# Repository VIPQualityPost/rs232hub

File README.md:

# rs232hub
This is a small project to make a USB-RS232 four port hub for use with SCPI commands for making an easy, automated testing controller. 
I successfully made the prototype with just one channel, but for the final design I want to incorporate a 4 port USB hub controller so I can have several devices connected at once.
I don't need USB3.0 speed so this will not include that, but it will feature a USB-C port to be consistent with other designs I have made (and I still have several connectors left over from previous projects)

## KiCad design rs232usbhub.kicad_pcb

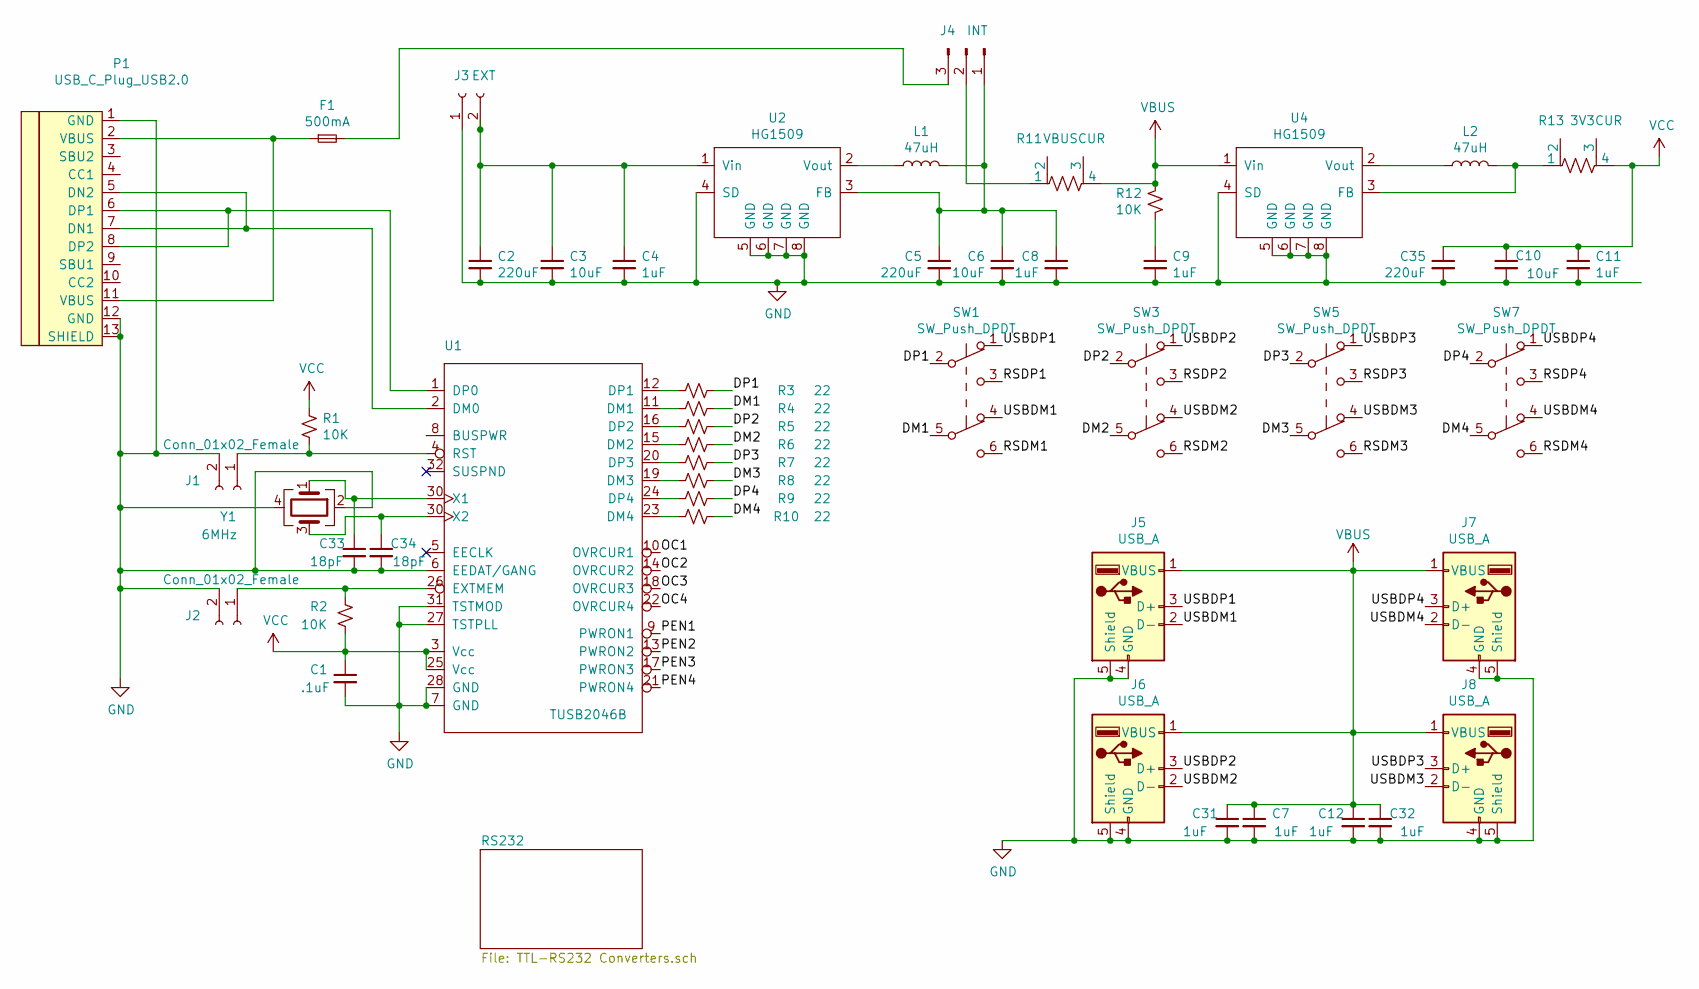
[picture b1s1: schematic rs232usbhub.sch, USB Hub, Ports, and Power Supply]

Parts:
C1: .1uF; C_0402_1005Metric_Pad0.74x0.62mm_HandSolder
C2, C5, C35: 220uF; CP_Elec_8x10.5
C3, C6, C10: 10uF; CP_Elec_4x5.4
C4, C7, C8, C9, C11, C12, C31, C32: 1uF; C_0402_1005Metric_Pad0.74x0.62mm_HandSolder
C33, C34: 18pF; C_0402_1005Metric_Pad0.74x0.62mm_HandSolder
F1: 500mA; C_0402_1005Metric_Pad0.74x0.62mm_HandSolder
J1, J2: Conn_01x02_Female; PinHeader_1x02_P1.00mm_Vertical
J3: EXT; BarrelJack_CLIFF_FC681465S_SMT_Horizontal
J4: INT; PinHeader_1x03_P2.54mm_Vertical
J5, J6, J7, J8: USB_A; USBA2LCSC109355
L1, L2: 47uH; L_12x12mm_H4.5mm
P1: USB_C_Plug_USB2.0; HRO-TYPE-C-31-M-12-HandSoldering
R1, R2, R12: 10K; R_0402_1005Metric_Pad0.72x0.64mm_HandSolder
R3, R4, R5, R6, R7, R8, R9, R10: 22; R_0402_1005Metric_Pad0.72x0.64mm_HandSolder
R11: VBUSCUR; R_0402_1005Metric_Pad0.72x0.64mm_HandSolder
R13: 3V3CUR; R_0402_1005Metric_Pad0.72x0.64mm_HandSolder
SW1, SW3, SW5, SW7: SW_Push_DPDT; SW_CuK_JS202011CQN_DPDT_Straight
U1: TUSB2046B; LQFP-32_7x7mm_P0.8mm
U2, U4: HG1509; SOP-8_3.9x4.9mm_P1.27mm
Y1: 6MHz; Crystal_SMD_EuroQuartz_MQ-4Pin_7.0x5.0mm_HandSoldering

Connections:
/DM1: R4.1, SW1.5 (B)
/DM2: R6.1, SW3.5 (B)
/DM3: R8.1, SW5.5 (B)
/DM4: R10.1, SW7.5 (B)
/DP1: R3.1, SW1.2 (B)
/DP2: R5.1, SW3.2 (B)
/DP3: R7.1, SW5.2 (B)
/DP4: R9.1, SW7.2 (B)
/OC1: U1.10 (OVRCUR1)
/OC2: U1.14 (OVRCUR2)
/OC3: U1.18 (OVRCUR3)
/OC4: U1.22 (OVRCUR4)
/PEN1: U1.9 (PWRON1)
/PEN2: U1.13 (PWRON2)
/PEN3: U1.17 (PWRON3)
/PEN4: U1.21 (PWRON4)
/RSDM1: SW1.6 (C)
/RSDM2: SW3.6 (C)
/RSDM3: SW5.6 (C)
/RSDM4: SW7.6 (C)
/RSDP1: SW1.3 (C)
/RSDP2: SW3.3 (C)
/RSDP3: SW5.3 (C)
/RSDP4: SW7.3 (C)
/USBDM1: J5.2 (D-), SW1.4 (A)
/USBDM2: J6.2 (D-), SW3.4 (A)
/USBDM3: J8.2 (D-), SW5.4 (A)
/USBDM4: J7.2 (D-), SW7.4 (A)
/USBDP1: J5.3 (D+), SW1.1 (A)
/USBDP2: J6.3 (D+), SW3.1 (A)
/USBDP3: J8.3 (D+), SW5.1 (A)
/USBDP4: J7.3 (D+), SW7.1 (A)
GND: C1.2, C2.2, C3.2, C4.2, C5.2, C6.2, C7.2, C8.2, C9.2, C10.2, C11.2, C12.2, C31.2, C32.2, C33.2, C34.2, C35.2, J1.2, J2.2, J3.1, J5.4 (GND), J5.5 (Shield), J6.4 (GND), J6.5 (Shield), J7.4 (GND), J7.5 (Shield), J8.4 (GND), J8.5 (Shield), P1.1 (GND), P1.12 (GND), P1.13 (SHIELD), U1.6 (EEDAT/GANG), U1.7 (GND), U1.27 (TSTPLL), U1.28 (GND), U1.31 (TSTMOD), U2.4 (SD), U2.5 (GND), U2.6 (GND), U2.7 (GND), U2.8 (GND), U4.4 (SD), U4.5 (GND), U4.6 (GND), U4.7 (GND), U4.8 (GND), Y1.2, Y1.4; also elsewhere on the board
unnamed: C2.1, C3.1, C4.1, J3.2, U2.1 (Vin)
unnamed: C5.1, C6.1, C8.1, J4.1, L1.2, U2.3 (FB)
unnamed: C9.1, R12.2
unnamed: F1.1, P1.2 (VBUS), P1.11 (VBUS)
unnamed: F1.2, J4.3
unnamed: J1.1, R1.2, U1.4 (RST)
unnamed: J2.1, R2.1, U1.26 (EXTMEM)
unnamed: J4.2, R11.1
unnamed: L1.1, U2.2 (Vout)
unnamed: L2.1, U4.2 (Vout)
unnamed: L2.2, R13.1, U4.3 (FB)
unnamed: P1.5 (DN2), P1.7 (DN1), U1.2 (DM0)
unnamed: P1.6 (DP1), P1.8 (DP2), U1.1 (DP0)
unnamed: R3.2, U1.12 (DP1)
unnamed: R4.2, U1.11 (DM1)
unnamed: R5.2, U1.16 (DP2)
unnamed: R6.2, U1.15 (DM2)
unnamed: R7.2, U1.20 (DP3)
unnamed: R8.2, U1.19 (DM3)
unnamed: R9.2, U1.24 (DP4)
unnamed: R10.2, U1.23 (DM4)
VBUS: C7.1, C12.1, C31.1, C32.1, J5.1 (VBUS), J6.1 (VBUS), J7.1 (VBUS), J8.1 (VBUS), R11.4, R12.1, U4.1 (Vin); also elsewhere on the board
VCC: C1.1, C10.1, C11.1, C35.1, R1.1, R2.2, R13.4, U1.3 (Vcc), U1.25 (Vcc)

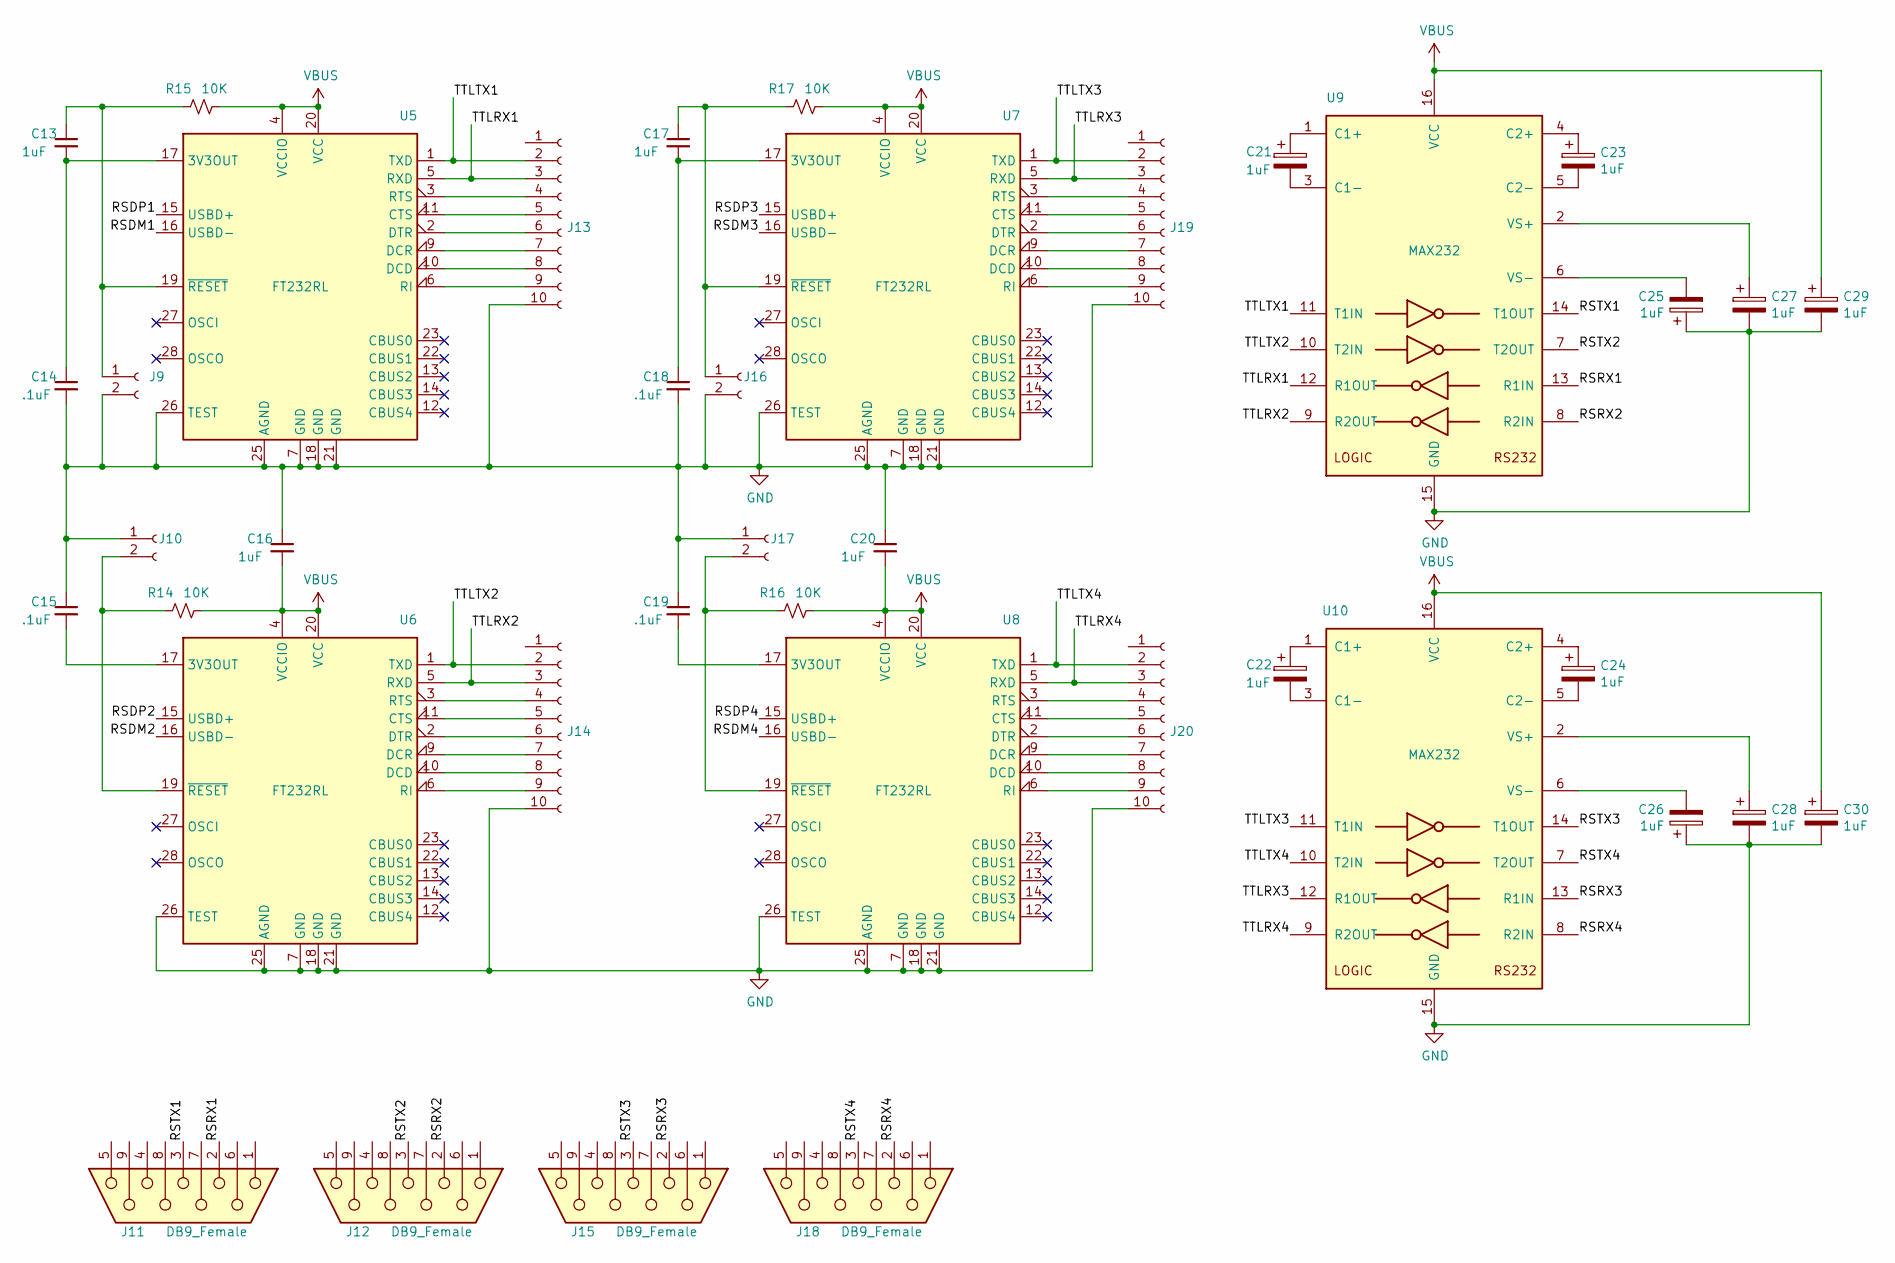
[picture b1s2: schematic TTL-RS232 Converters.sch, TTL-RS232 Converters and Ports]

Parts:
C13, C16, C17, C20: 1uF; C_0402_1005Metric_Pad0.74x0.62mm_HandSolder
C14, C15, C18, C19: .1uF; C_0402_1005Metric_Pad0.74x0.62mm_HandSolder
C21, C22, C23, C24, C25, C26, C27, C28, C29, C30: 1uF; CP_Elec_4x5.4
J9, J10, J16, J17: Conn_01x02_Female; PinHeader_1x02_P1.00mm_Vertical
J11, J12, J15, J18: DB9_Female; dsub9
J13, J14, J19, J20: Conn_01x10_Female; PinSocket_1x10_P2.54mm_Vertical
R14, R15, R16, R17: 10K; R_0402_1005Metric_Pad0.72x0.64mm_HandSolder
U5, U6, U7, U8: FT232RL; SSOP-28_5.3x10.2mm_P0.65mm
U9, U10: MAX232; SOIC-16_3.9x9.9mm_P1.27mm

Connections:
/RS232/RSDM1: U5.16 (USBD-)
/RS232/RSDM2: U6.16 (USBD-)
/RS232/RSDM3: U7.16 (USBD-)
/RS232/RSDM4: U8.16 (USBD-)
/RS232/RSDP1: U5.15 (USBD+)
/RS232/RSDP2: U6.15 (USBD+)
/RS232/RSDP3: U7.15 (USBD+)
/RS232/RSDP4: U8.15 (USBD+)
/RS232/RSRX1: J11.2, U9.13 (R1IN)
/RS232/RSRX2: J12.2, U9.8 (R2IN)
/RS232/RSRX3: J15.2, U10.13 (R1IN)
/RS232/RSRX4: J18.2, U10.8 (R2IN)
/RS232/RSTX1: J11.3, U9.14 (T1OUT)
/RS232/RSTX2: J12.3, U9.7 (T2OUT)
/RS232/RSTX3: J15.3, U10.14 (T1OUT)
/RS232/RSTX4: J18.3, U10.7 (T2OUT)
/RS232/TTLRX1: J13.3, U5.5 (RXD), U9.12 (R1OUT)
/RS232/TTLRX2: J14.3, U6.5 (RXD), U9.9 (R2OUT)
/RS232/TTLRX3: J19.3, U7.5 (RXD), U10.12 (R1OUT)
/RS232/TTLRX4: J20.3, U8.5 (RXD), U10.9 (R2OUT)
/RS232/TTLTX1: J13.2, U5.1 (TXD), U9.11 (T1IN)
/RS232/TTLTX2: J14.2, U6.1 (TXD), U9.10 (T2IN)
/RS232/TTLTX3: J19.2, U7.1 (TXD), U10.11 (T1IN)
/RS232/TTLTX4: J20.2, U8.1 (TXD), U10.10 (T2IN)
GND: C14.2, C15.1, C16.1, C18.2, C19.1, C20.1, C25.1, C26.1, C27.2, C28.2, C29.2, C30.2, J9.2, J10.1, J13.10, J14.10, J16.2, J17.1, J19.10, J20.10, U5.7 (GND), U5.18 (GND), U5.21 (GND), U5.25 (AGND), U5.26 (TEST), U6.7 (GND), U6.18 (GND), U6.21 (GND), U6.25 (AGND), U6.26 (TEST), U7.7 (GND), U7.18 (GND), U7.21 (GND), U7.25 (AGND), U7.26 (TEST), U8.7 (GND), U8.18 (GND), U8.21 (GND), U8.25 (AGND), U8.26 (TEST), U9.15 (GND), U10.15 (GND); also elsewhere on the board
unnamed: C13.1, J9.1, R15.1, U5.19 (~RESET~)
unnamed: C13.2, C14.1, U5.17 (3V3OUT)
unnamed: C15.2, U6.17 (3V3OUT)
unnamed: C17.1, J16.1, R17.1, U7.19 (~RESET~)
unnamed: C17.2, C18.1, U7.17 (3V3OUT)
unnamed: C19.2, U8.17 (3V3OUT)
unnamed: C21.1, U9.1 (C1+)
unnamed: C21.2, U9.3 (C1-)
unnamed: C22.1, U10.1 (C1+)
unnamed: C22.2, U10.3 (C1-)
unnamed: C23.1, U9.4 (C2+)
unnamed: C23.2, U9.5 (C2-)
unnamed: C24.1, U10.4 (C2+)
unnamed: C24.2, U10.5 (C2-)
unnamed: C25.2, U9.6 (VS-)
unnamed: C26.2, U10.6 (VS-)
unnamed: C27.1, U9.2 (VS+)
unnamed: C28.1, U10.2 (VS+)
unnamed: J10.2, R14.1, U6.19 (~RESET~)
unnamed: J13.4, U5.3 (RTS)
unnamed: J13.5, U5.11 (CTS)
unnamed: J13.6, U5.2 (DTR)
unnamed: J13.7, U5.9 (DCR)
unnamed: J13.8, U5.10 (DCD)
unnamed: J13.9, U5.6 (RI)
unnamed: J14.4, U6.3 (RTS)
unnamed: J14.5, U6.11 (CTS)
unnamed: J14.6, U6.2 (DTR)
unnamed: J14.7, U6.9 (DCR)
unnamed: J14.8, U6.10 (DCD)
unnamed: J14.9, U6.6 (RI)
unnamed: J17.2, R16.1, U8.19 (~RESET~)
unnamed: J19.4, U7.3 (RTS)
unnamed: J19.5, U7.11 (CTS)
unnamed: J19.6, U7.2 (DTR)
unnamed: J19.7, U7.9 (DCR)
unnamed: J19.8, U7.10 (DCD)
unnamed: J19.9, U7.6 (RI)
unnamed: J20.4, U8.3 (RTS)
unnamed: J20.5, U8.11 (CTS)
unnamed: J20.6, U8.2 (DTR)
unnamed: J20.7, U8.9 (DCR)
unnamed: J20.8, U8.10 (DCD)
unnamed: J20.9, U8.6 (RI)
VBUS: C16.2, C20.2, C29.1, C30.1, R14.2, R15.2, R16.2, R17.2, U5.4 (VCCIO), U5.20 (VCC), U6.4 (VCCIO), U6.20 (VCC), U7.4 (VCCIO), U7.20 (VCC), U8.4 (VCCIO), U8.20 (VCC), U9.16 (VCC), U10.16 (VCC); also elsewhere on the board

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
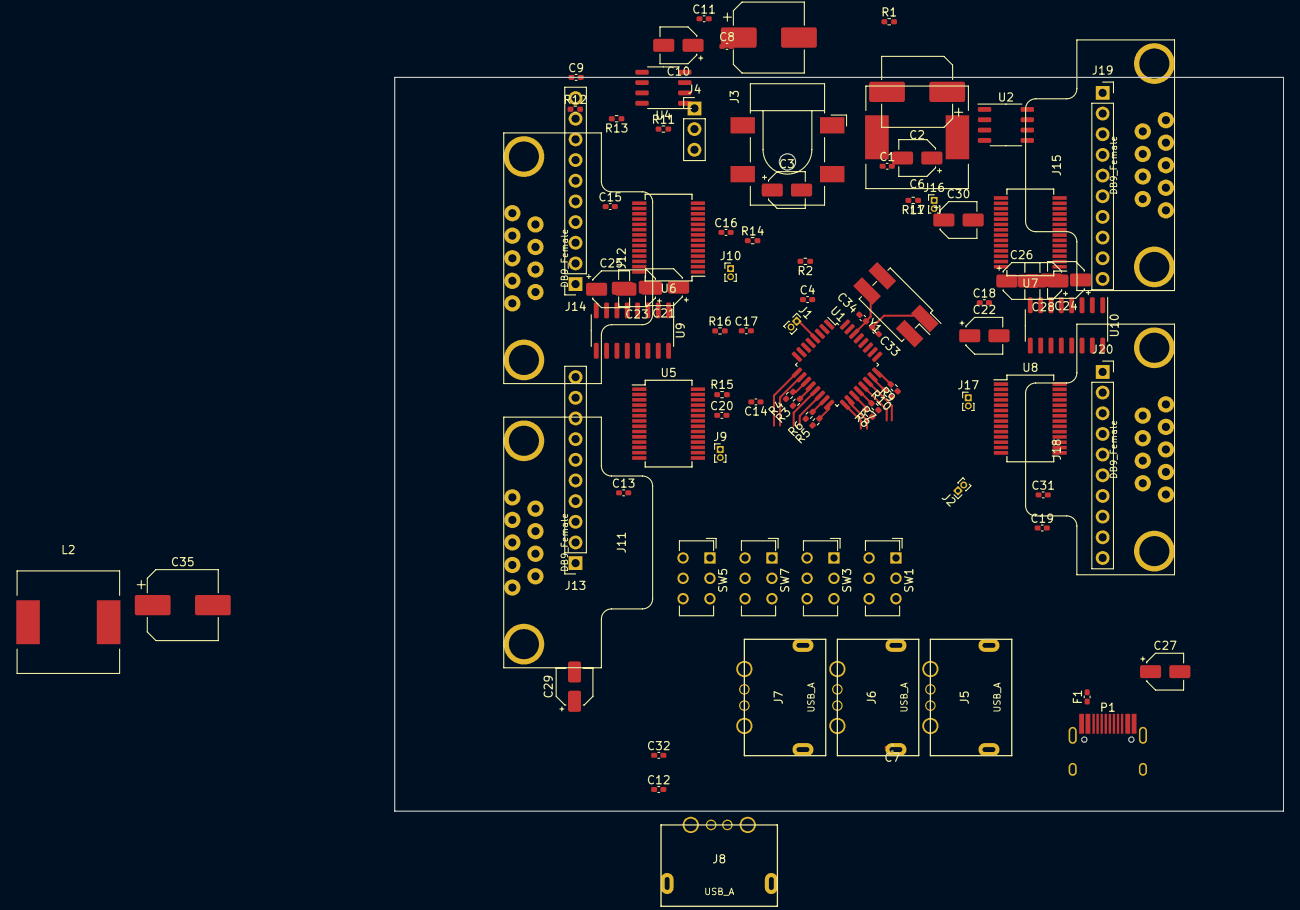
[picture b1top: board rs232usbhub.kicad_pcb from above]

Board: 2 copper layers, 109.2 x 90.2 mm, 90 parts (0 on the bottom side), 102 nets.
